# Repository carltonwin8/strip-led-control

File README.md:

# LED Light Strip Control

Use the raspberry pi to control a LED light strip.

## Schematic

| Schematic | Board |
| --- | --- |
|  |  |

The test LED circuit between J1 and J2 is replaced with LED strip for actual use.

## Implementation Plan

All phases not shown are done.

### Phase 5

Write software to allow Internet control of the board.

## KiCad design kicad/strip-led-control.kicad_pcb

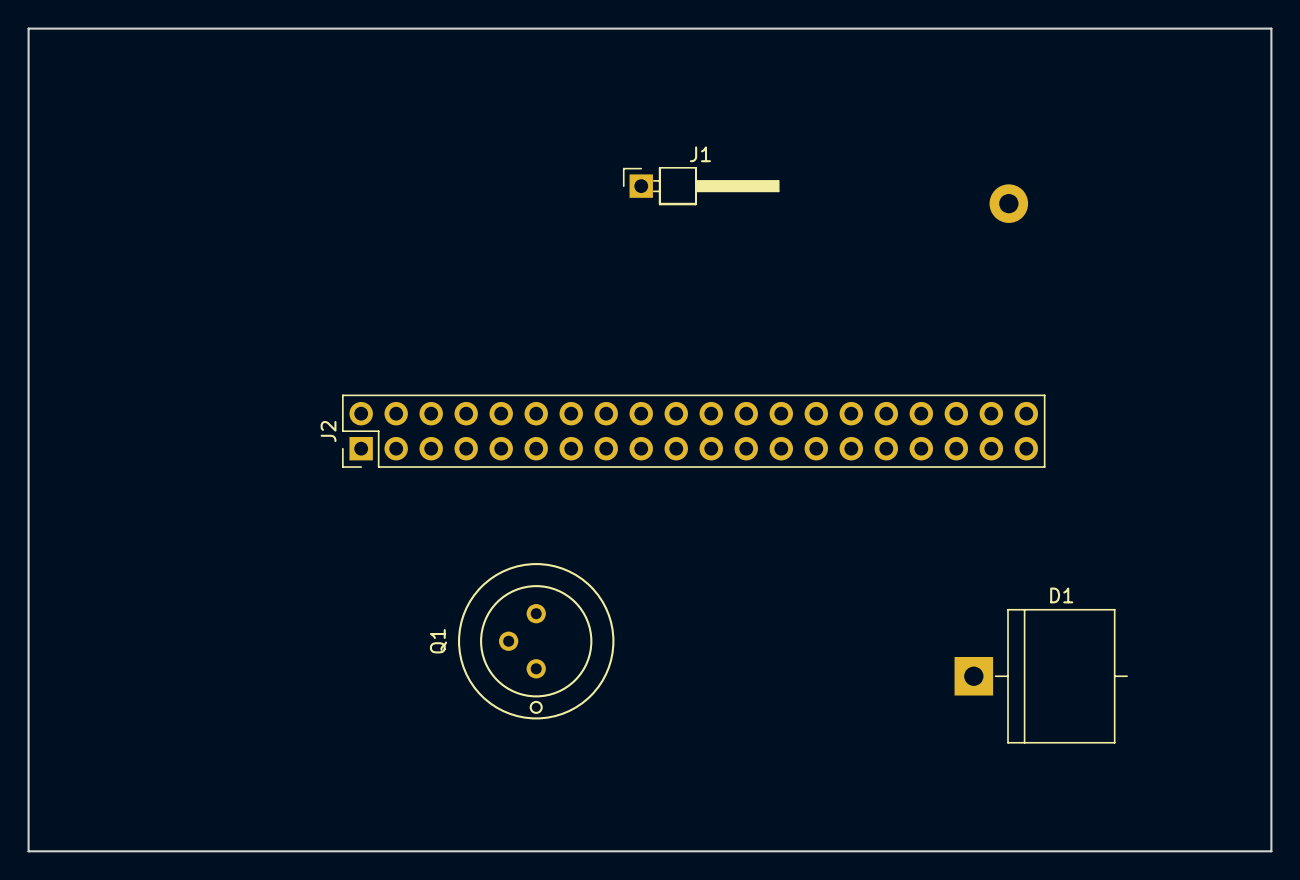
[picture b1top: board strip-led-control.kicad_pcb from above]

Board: 2 copper layers, 90.2 x 59.7 mm, 4 parts (0 on the bottom side), 5 nets, no tracks yet.

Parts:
D1: LED; D_5KP_P12.70mm_Horizontal
J1: CONN_01X02; Pin_Header_Angled_1x01_Pitch2.54mm
J2: Raspberry_Pi_2_3; Pin_Header_Straight_2x20_Pitch2.54mm
Q1: Q_NPN_ECB; OldSowjetaera_Transistor_Type-II_SmallPads

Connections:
+3V3: J2.1, J2.17
+5V: J2.2, J2.4
/copip: J2.11, Q1.3
GND: D1.1, J1.1, J2.39
unnamed: D1.2, Q1.1

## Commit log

2017-04-05 initial code commit
2017-04-07 add schematic and updated code
2017-04-07 add software to test hardware design works
2017-04-08 add code for glow and dual led
2017-04-10 add more incorrect circuit designs
2017-04-13 added code for glowing leds
2017-04-13 update dual glowing led code
